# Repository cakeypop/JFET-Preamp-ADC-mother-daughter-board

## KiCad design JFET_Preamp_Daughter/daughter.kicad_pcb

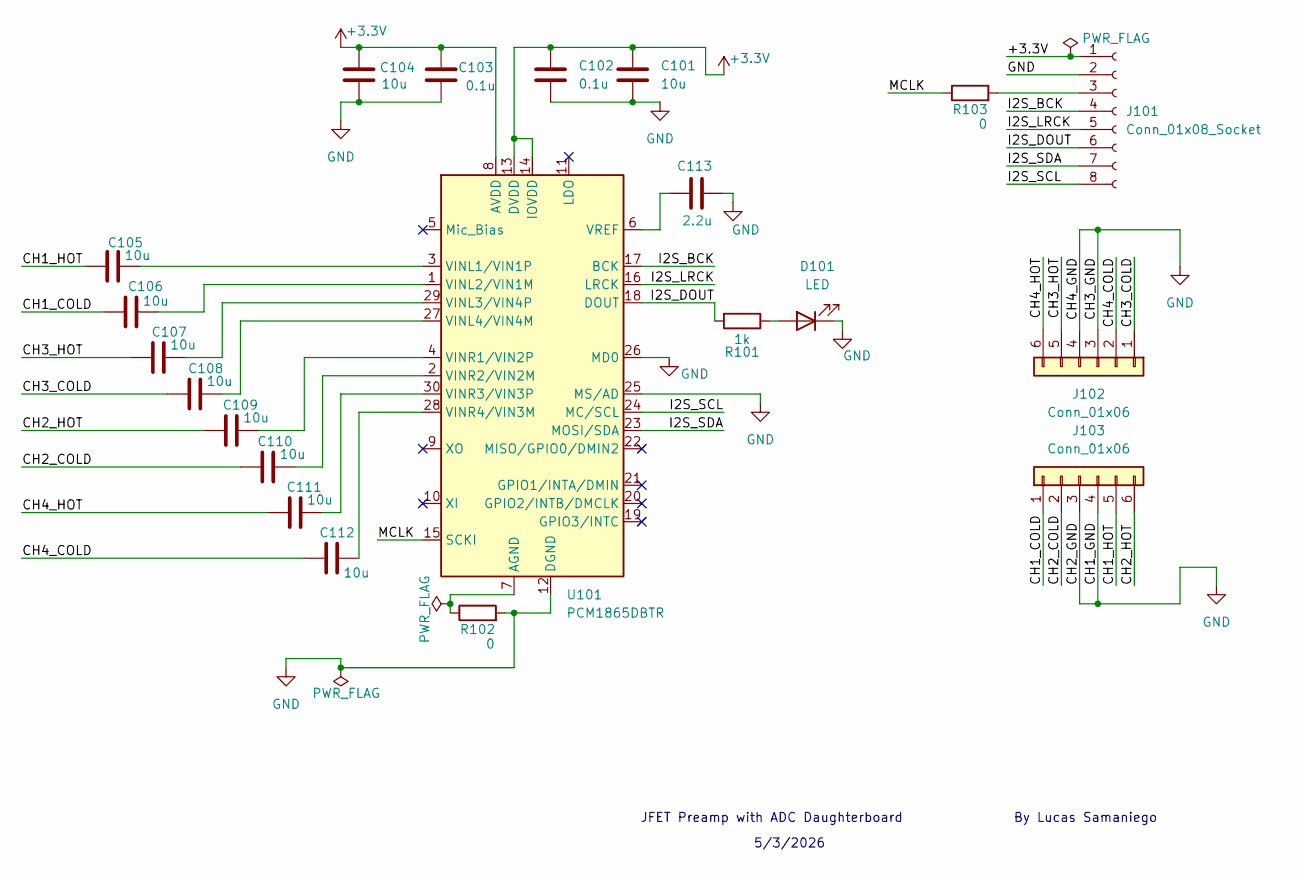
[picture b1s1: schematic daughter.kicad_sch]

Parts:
C101, C104, C105, C106, C107, C108, C109, C110, C111, C112: 10u; C_0402_1005Metric; LCSC Part # C15525
C102, C103: 0.1u; C_0402_1005Metric; LCSC Part # C1525
C113: 2.2u; C_0402_1005Metric; LCSC Part # C12530
D101: LED; LED_0603_1608Metric; LCSC Part # C2286
J101: Conn_01x08_Socket; JST_GH_BM08B-GHS-TBT_1x08-1MP_P1.25mm_Vertical
J102, J103: Conn_01x06; PinHeader_1x06_P2.54mm_Vertical
R101: 1k; R_0603_1608Metric; LCSC Part # C21190
R102, R103: 0; R_0603_1608Metric; LCSC Part # C21189
U101: PCM1865DBTR; TSSOP-30_4.4x7.8mm_P0.5mm; LCSC Part # C181312

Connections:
+3.3V: C101.1, C102.1, C103.1, C104.1, J101.1, U101.8 (AVDD), U101.13 (DVDD), U101.14 (IOVDD)
/CH1_COLD: C106.1, J103.1
/CH1_HOT: C105.1, J103.5
/CH2_COLD: C110.1, J103.2
/CH2_HOT: C109.1, J103.6
/CH3_COLD: C108.1, J102.1
/CH3_HOT: C107.1, J102.5
/CH4_COLD: C112.1, J102.2
/CH4_HOT: C111.1, J102.6
/I2S_BCK: J101.4, U101.17 (BCK)
/I2S_DOUT: J101.6, R101.2, U101.18 (DOUT)
/I2S_LRCK: J101.5, U101.16 (LRCK)
/I2S_SCL: J101.8, U101.24 (MC/SCL)
/I2S_SDA: J101.7, U101.23 (MOSI/SDA)
/MCLK: R103.1, U101.15 (SCKI)
GND: C101.2, C102.2, C103.2, C104.2, C113.2, D101.1 (K), J101.2, J102.3, J102.4, J103.3, J103.4, R102.2, U101.12 (DGND), U101.25 (MS/AD), U101.26 (MD0)
unnamed: D101.2 (A), R101.1
unnamed: J101.3, R103.2
unnamed: R102.1, U101.7 (AGND)
unnamed: C105.2, U101.3 (VINL1/VIN1P)
unnamed: C106.2, U101.1 (VINL2/VIN1M)
unnamed: C107.2, U101.29 (VINL3/VIN4P)
unnamed: C108.2, U101.27 (VINL4/VIN4M)
unnamed: C109.2, U101.4 (VINR1/VIN2P)
unnamed: C110.2, U101.2 (VINR2/VIN2M)
unnamed: C111.2, U101.30 (VINR3/VIN3P)
unnamed: C112.2, U101.28 (VINR4/VIN3M)
unnamed: C113.1, U101.6 (VREF)

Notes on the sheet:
JFET Preamp with ADC Daughterboard By Lucas Samaniego
5/3/2026

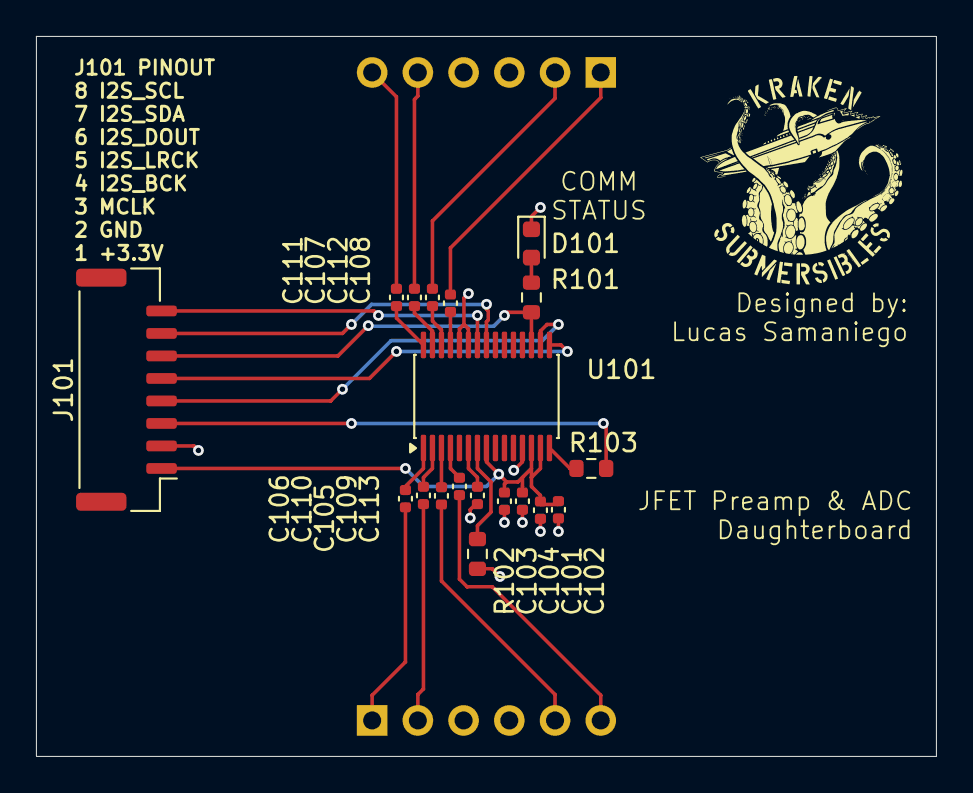
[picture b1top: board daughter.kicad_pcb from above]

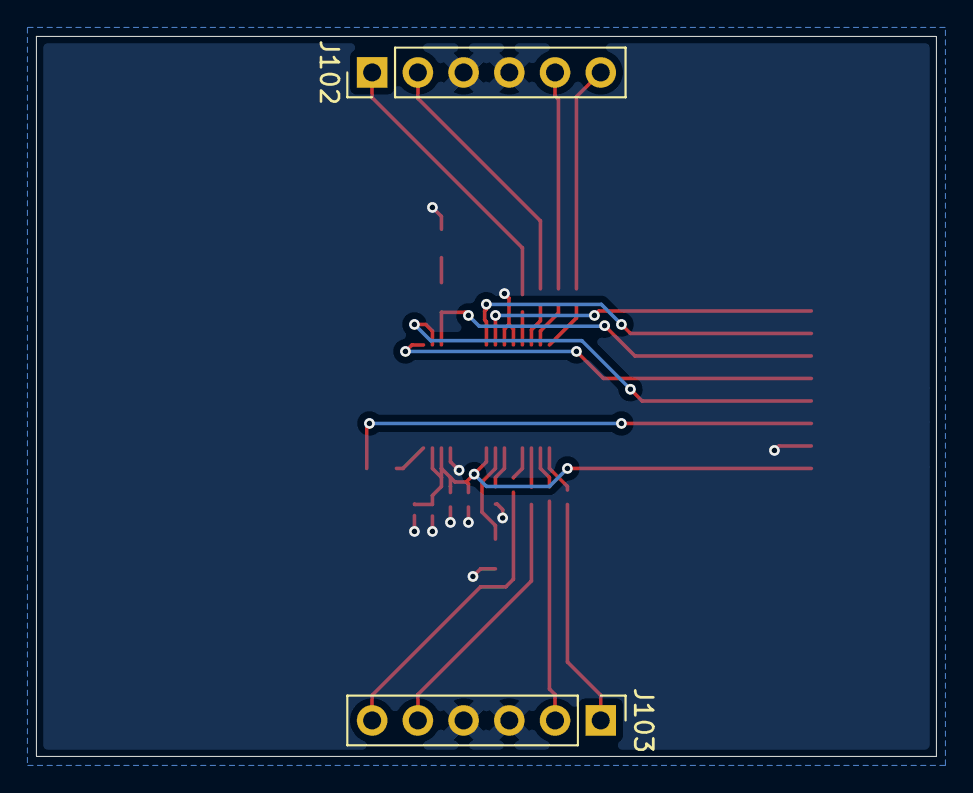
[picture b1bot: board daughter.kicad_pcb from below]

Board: 2 copper layers, 50.0 x 40.0 mm, 21 parts (2 on the bottom side), 28 nets.

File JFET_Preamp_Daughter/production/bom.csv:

Designator,Footprint,Quantity,Value,LCSC Part #
"C101, C104, C105, C106, C107, C108, C109, C110, C111, C112",0402,10,10u,C15525
"C102, C103",0402,2,0.1u,C1525 
C113,0402,1,2.2u,C12530
D101,0603,1,LED,C2286
R101,0603,1,1k,C21190
"R102, R103",0603,2,0,C21189
U101,TSSOP-30_4.4x7.8mm_P0.5mm,1,PCM1865DBTR,C181312

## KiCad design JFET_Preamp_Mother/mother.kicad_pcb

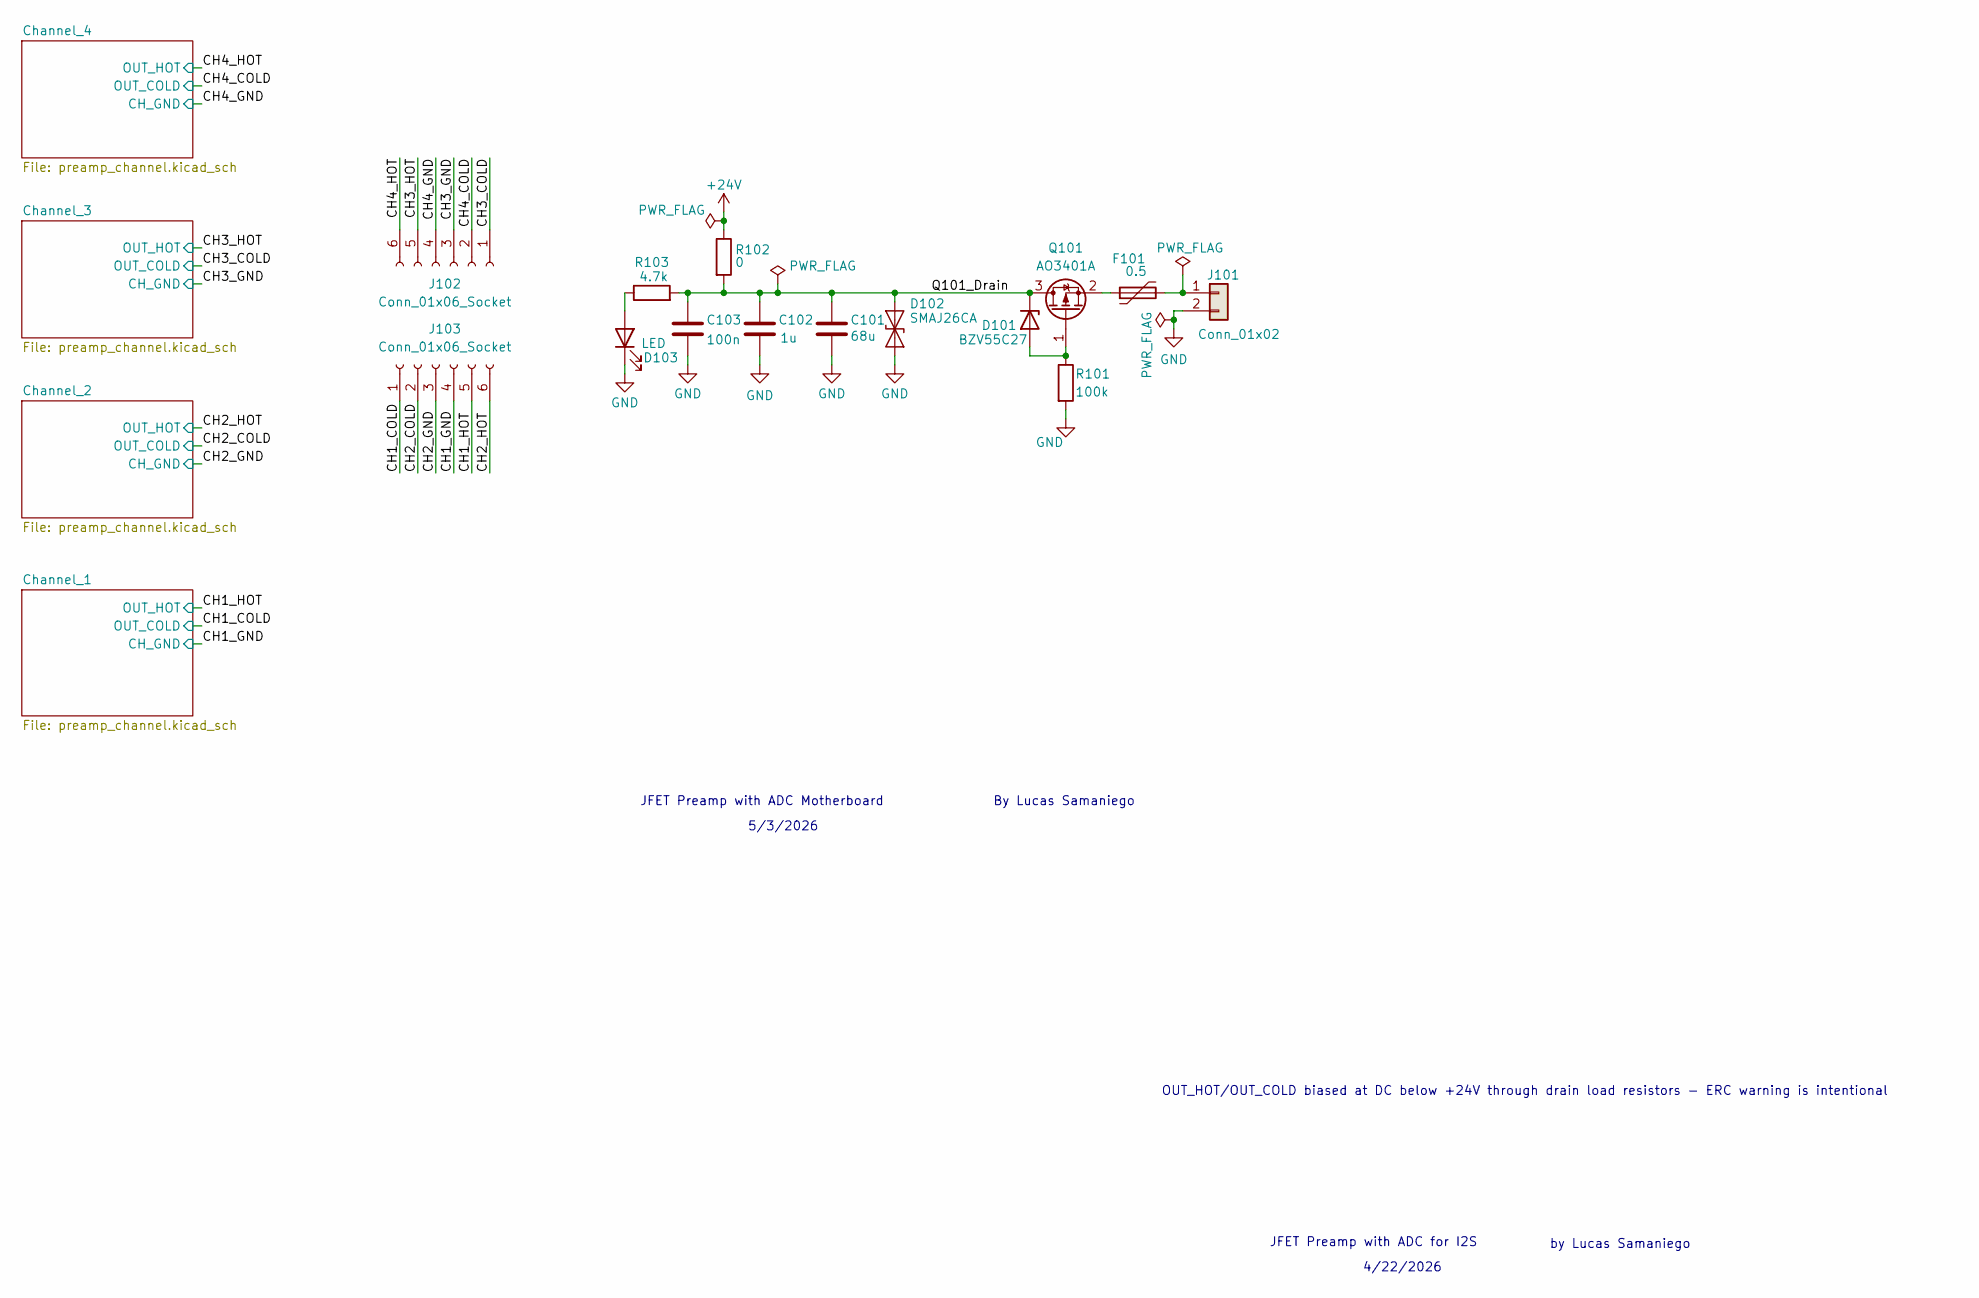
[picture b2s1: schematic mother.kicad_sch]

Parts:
C101: 68u; CP_Elec_6.3x5.4
C102: 1u; C_0603_1608Metric; LCSC Part # C15849
C103: 100n; C_0603_1608Metric; LCSC Part # C14663
D101: BZV55C27; D_MiniMELF; LCSC Part # C545374
D102: SMAJ26CA; D_SMA; LCSC Part # C148226
D103: LED; LED_0603_1608Metric; LCSC Part # C2286
F101: 0.5; FUSRB510W51L790T310H1370
J101: Conn_01x02; PinHeader_1x02_P2.54mm_Vertical
J102, J103: Conn_01x06_Socket; PinSocket_1x06_P2.54mm_Vertical
Q101: AO3401A; SOT-23; LCSC Part # C15127
R101: 100k; R_0603_1608Metric; LCSC Part # C25803
R102: 0; R_0603_1608Metric; LCSC Part # C21189
R103: 4.7k; R_0603_1608Metric; LCSC Part # C25999

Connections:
+24V: R102.1; also elsewhere on the board
/CH1_COLD: J103.1; also elsewhere on the board
/CH1_GND: J103.4; also elsewhere on the board
/CH1_HOT: J103.5; also elsewhere on the board
/CH2_COLD: J103.2; also elsewhere on the board
/CH2_GND: J103.3; also elsewhere on the board
/CH2_HOT: J103.6; also elsewhere on the board
/CH3_COLD: J102.1; also elsewhere on the board
/CH3_GND: J102.3; also elsewhere on the board
/CH3_HOT: J102.5; also elsewhere on the board
/CH4_COLD: J102.2; also elsewhere on the board
/CH4_GND: J102.4; also elsewhere on the board
/CH4_HOT: J102.6; also elsewhere on the board
/Q101_Drain: C101.1, C102.1, C103.1, D101.1 (K), D102.2 (A2), Q101.3 (D), R102.2, R103.2
GND: C101.2, C102.2, C103.2, D102.1 (A1), D103.1 (K), J101.2, R101.2
unnamed: D101.2 (A), Q101.1 (G), R101.1
unnamed: D103.2 (A), R103.1
unnamed: F101.2, J101.1
unnamed: F101.1, Q101.2 (S)

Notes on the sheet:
OUT_HOT/OUT_COLD biased at DC below +24V through drain load resistors - ERC warning is intentional
JFET Preamp with ADC for I2S
5/3/2026
by Lucas Samaniego
JFET Preamp with ADC Motherboard By Lucas Samaniego
4/22/2026

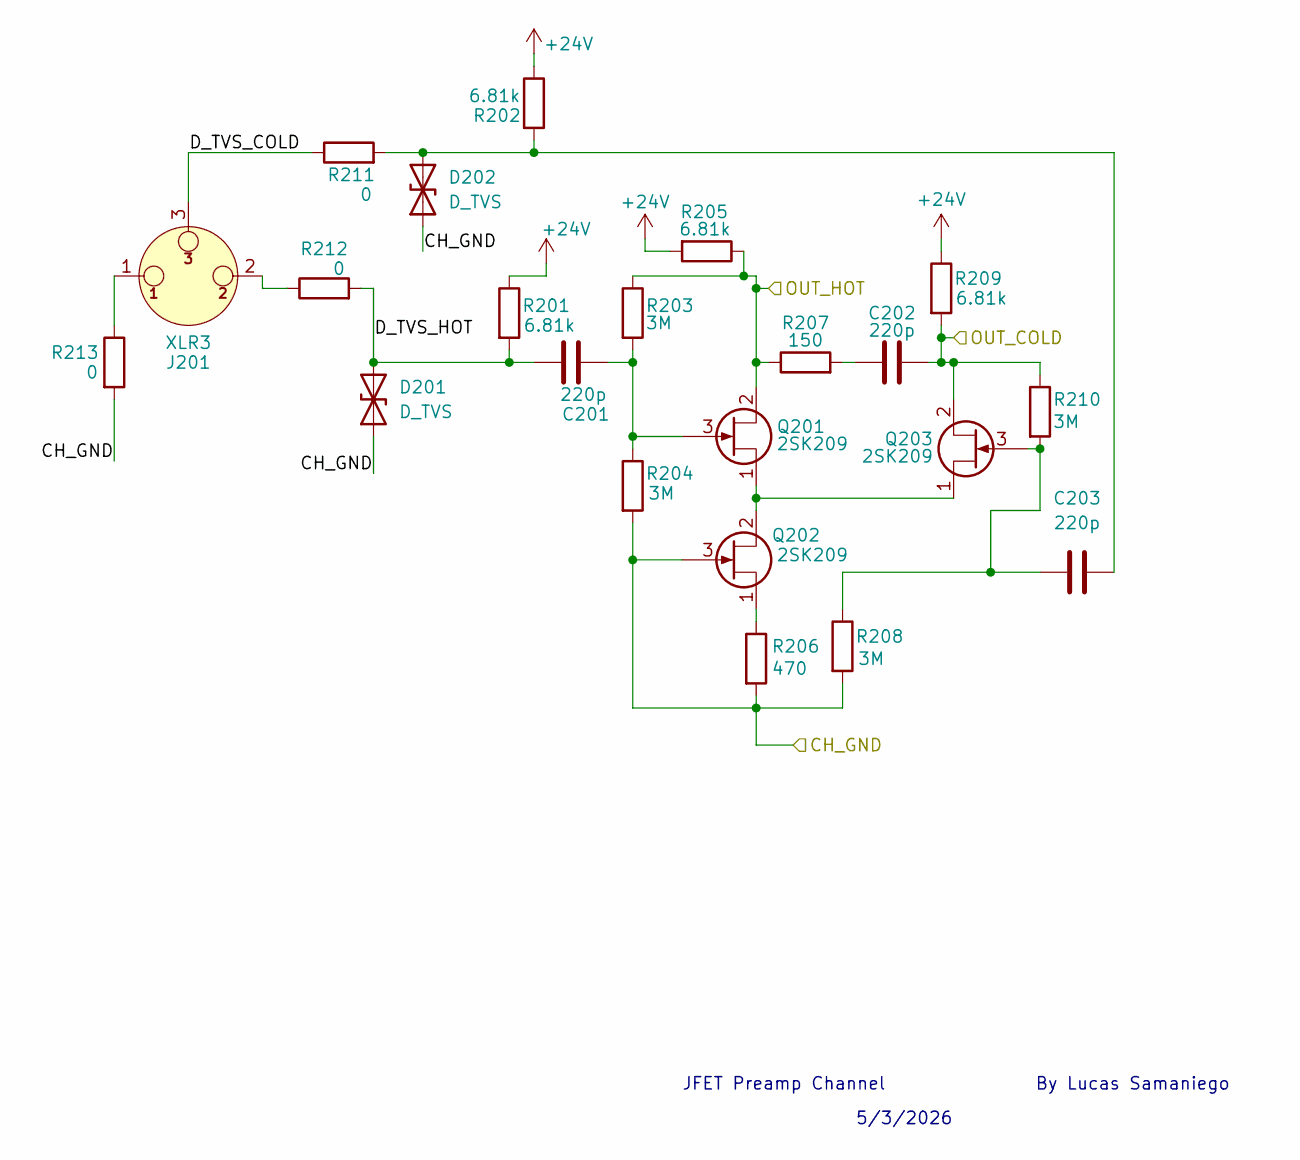
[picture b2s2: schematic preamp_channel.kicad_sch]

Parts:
C201, C202, C203: 220p; C_0603_1608Metric; LCSC Part # C1603
D201, D202: D_TVS; D_SMA; LCSC Part # C148226
J201: XLR3; Jack_XLR_Neutrik_NC3FAH1_Horizontal
Q201, Q202, Q203: 2SK209; SOT-23; LCSC Part # C2880444
R201, R202, R205, R209: 6.81k; R_0603_1608Metric; LCSC Part # C137687
R203, R204, R208, R210: 3M; R_0603_1608Metric; LCSC Part # C23156
R206: 470; R_0603_1608Metric; LCSC Part # C25117
R207: 150; R_0603_1608Metric; LCSC Part # C22808
R211, R212, R213: 0; R_0603_1608Metric; LCSC Part # C21189

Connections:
+24V: R201.1, R202.1, R205.2, R209.1; also elsewhere on the board
/CH1_COLD: C202.2, Q203.2 (D), R209.2, R210.1; also elsewhere on the board
/CH1_GND: D201.1 (A1), D202.1 (A1), Q202.3 (G), R204.2, R206.2, R208.2, R213.2; also elsewhere on the board
/CH1_HOT: Q201.2 (D), R203.1, R205.1, R207.1; also elsewhere on the board
/Channel_1/D_TVS_COLD: J201.3, R211.1
/Channel_1/D_TVS_HOT: C201.1, D201.2 (A2), R201.2, R212.2
unnamed: C202.1, R207.2
unnamed: C203.2, D202.2 (A2), R202.2, R211.2
unnamed: J201.1, R213.1
unnamed: J201.2, R212.1
unnamed: C201.2, Q201.3 (G), R203.2, R204.1
unnamed: Q201.1 (S), Q202.2 (D), Q203.1 (S)
unnamed: Q202.1 (S), R206.1
unnamed: C203.1, Q203.3 (G), R208.1, R210.2

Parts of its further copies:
C301, C302, C303, C401, C402, C403, C501, C502, C503: 220p; C_0603_1608Metric; LCSC Part # C1603
D301, D302, D401, D402, D501, D502: D_TVS; D_SMA; LCSC Part # C148226
J301, J401, J501: XLR3; Jack_XLR_Neutrik_NC3FAH1_Horizontal
Q301, Q302, Q303, Q401, Q402, Q403, Q501, Q502, Q503: 2SK209; SOT-23; LCSC Part # C2880444
R301, R302, R305, R309, R401, R402, R405, R409, R501, R502, R505, R509: 6.81k; R_0603_1608Metric; LCSC Part # C137687
R303, R304, R308, R310, R403, R404, R408, R410, R503, R504, R508, R510: 3M; R_0603_1608Metric; LCSC Part # C23156
R306, R406, R506: 470; R_0603_1608Metric; LCSC Part # C25117
R307, R407, R507: 150; R_0603_1608Metric; LCSC Part # C22808
R311, R312, R313, R411, R412, R413, R511, R512, R513: 0; R_0603_1608Metric; LCSC Part # C21189

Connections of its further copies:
+24V: R301.1, R302.1, R305.2, R309.1, R401.1, R402.1, R405.2, R409.1, R501.1, R502.1, R505.2, R509.1; also elsewhere on the board
/CH2_COLD: C302.2, Q303.2 (D), R309.2, R310.1; also elsewhere on the board
/CH2_GND: D301.1 (A1), D302.1 (A1), Q302.3 (G), R304.2, R306.2, R308.2, R313.2; also elsewhere on the board
/CH2_HOT: Q301.2 (D), R303.1, R305.1, R307.1; also elsewhere on the board
/CH3_COLD: C402.2, Q403.2 (D), R409.2, R410.1; also elsewhere on the board
/CH3_GND: D401.1 (A1), D402.1 (A1), Q402.3 (G), R404.2, R406.2, R408.2, R413.2; also elsewhere on the board
/CH3_HOT: Q401.2 (D), R403.1, R405.1, R407.1; also elsewhere on the board
/CH4_COLD: C502.2, Q503.2 (D), R509.2, R510.1; also elsewhere on the board
/CH4_GND: D501.1 (A1), D502.1 (A1), Q502.3 (G), R504.2, R506.2, R508.2, R513.2; also elsewhere on the board
/CH4_HOT: Q501.2 (D), R503.1, R505.1, R507.1; also elsewhere on the board
/Channel_2/D_TVS_COLD: J301.3, R311.1
/Channel_2/D_TVS_HOT: C301.1, D301.2 (A2), R301.2, R312.2
/Channel_3/D_TVS_COLD: J401.3, R411.1
/Channel_3/D_TVS_HOT: C401.1, D401.2 (A2), R401.2, R412.2
/Channel_4/D_TVS_COLD: J501.3, R511.1
/Channel_4/D_TVS_HOT: C501.1, D501.2 (A2), R501.2, R512.2
unnamed: C302.1, R307.2
unnamed: C402.1, R407.2
unnamed: C502.1, R507.2
unnamed: C303.2, D302.2 (A2), R302.2, R311.2
unnamed: C403.2, D402.2 (A2), R402.2, R411.2
unnamed: C503.2, D502.2 (A2), R502.2, R511.2
unnamed: J301.1, R313.1
unnamed: J301.2, R312.1
unnamed: J401.1, R413.1
unnamed: J401.2, R412.1
unnamed: J501.1, R513.1
unnamed: J501.2, R512.1
unnamed: C301.2, Q301.3 (G), R303.2, R304.1
unnamed: Q301.1 (S), Q302.2 (D), Q303.1 (S)
unnamed: Q302.1 (S), R306.1
unnamed: C303.1, Q303.3 (G), R308.1, R310.2
unnamed: C401.2, Q401.3 (G), R403.2, R404.1
unnamed: Q401.1 (S), Q402.2 (D), Q403.1 (S)
unnamed: Q402.1 (S), R406.1
unnamed: C403.1, Q403.3 (G), R408.1, R410.2
unnamed: C501.2, Q501.3 (G), R503.2, R504.1
unnamed: Q501.1 (S), Q502.2 (D), Q503.1 (S)
unnamed: Q502.1 (S), R506.1
unnamed: C503.1, Q503.3 (G), R508.1, R510.2

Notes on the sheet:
5/3/2026
JFET Preamp Channel By Lucas Samaniego

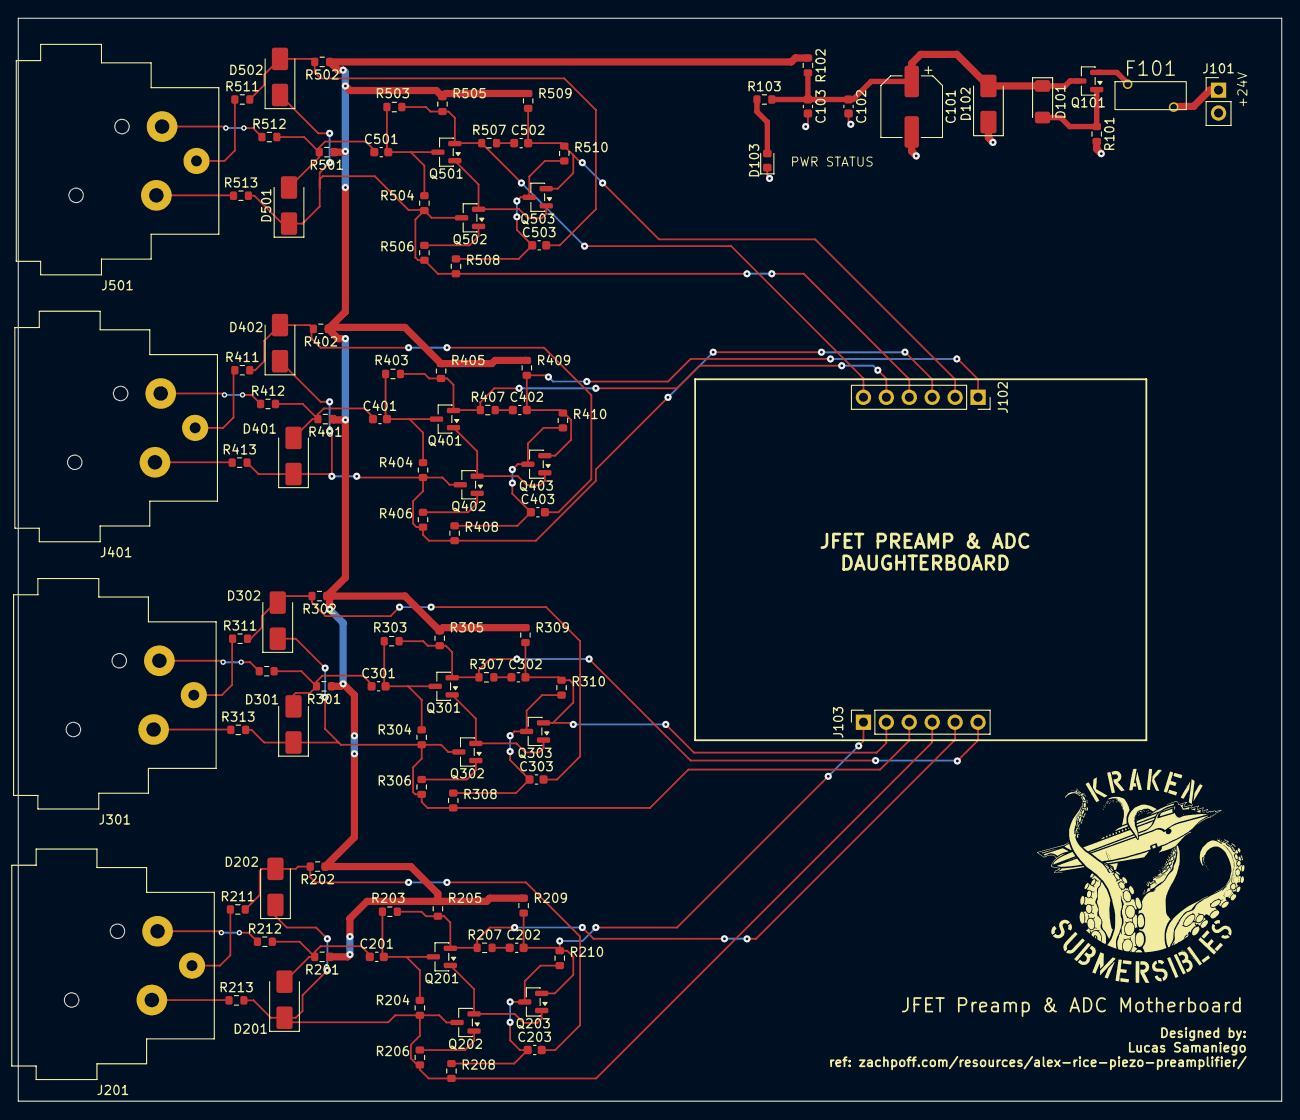
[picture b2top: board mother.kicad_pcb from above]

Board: 2 copper layers, 140.0 x 120.0 mm, 102 parts (0 on the bottom side), 59 nets.

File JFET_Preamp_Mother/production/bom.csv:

Designator,Footprint,Quantity,Value,LCSC Part #
C102,0603,1,1u,C15849
C103,0603,1,100n,C14663
"C201, C202, C203, C301, C302, C303, C401, C402, C403, C501, C502, C503",0603,12,220p,C1603
D101,D_MiniMELF,1,BZV55C27,C545374
D102,D_SMA,1,SMAJ26CA,C148226
D103,0603,1,LED,C2286
"D201, D202, D301, D302, D401, D402, D501, D502",D_SMA,8,D_TVS,C148226 
Q101,SOT-23,1,AO3401A,C15127
"Q201, Q202, Q203, Q301, Q302, Q303, Q401, Q402, Q403, Q501, Q502, Q503",SOT-23,12,2SK209,C2880444
R101,0603,1,100k,C25803
"R102, R211, R212, R213, R311, R312, R313, R411, R412, R413, R511, R512, R513",0603,13,0,C21189
R103,0603,1,4.7k,C25999
"R201, R202, R205, R209, R301, R302, R305, R309, R401, R402, R405, R409, R501, R502, R505, R509",0603,16,6.81k,C137687
"R203, R204, R208, R210, R303, R304, R308, R310, R403, R404, R408, R410, R503, R504, R508, R510",0603,16,3M,C23156
"R206, R306, R406, R506",0603,4,470,C25117
"R207, R307, R407, R507",0603,4,150,C22808

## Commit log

2026-06-17 Re-Initial commit after errors - mobo/daughter projects
2026-06-17 motherboard .sch erc clean
2026-06-17 Remove KiCad lock files from tracking, update gitignore
2026-06-17 Remove VS Code history folders and stray file from tracking
2026-06-17 Remove mother .history folder from tracking
2026-06-17 move MF-R050 footprint library into repo to use relative path
2026-06-17 daugter removed unused copy of preamp_channel.sch not used in daughterboard
2026-06-18 slight details update to daughter
2026-06-18 finish draft of mother/daughter sch and start routing, reconcile libraries and missing footprints
2026-06-18 adding a few minor edits
2026-06-19 finish routing daughterboard and fix 0 ohm resistor on AGND/DGND for schematic
2026-06-19 add silkscreen to pcb daughterboard, possibly final pending review
2026-06-19 fix ERC on schematic, then proceed to begin routing on pcb
2026-06-19 forgot to save ERC change adding pwr flag to mother sch
2026-06-24 push just to make sure everything is up to date
2026-06-30 WIP motherboard pcb save point, layout and partial routing complete
2026-06-30 fix backwards J102 on daughterboard to match schematic and mother/daughter pairing
2026-06-30 finished pcb, updated schematic formatting, ready for fab
2026-06-30 small updates to schematic before adjusting/printing pdf
2026-06-30 further adjustments to sch/pcb
2026-06-30 fixed wrong-facing 6pin connector and redo GND pour
2026-06-30 generate gerber and drill files
2026-06-30 fix error in gerber, extra layers
2026-06-30 regenerate mother gerber and drill
2026-06-30 fixed TVS Diodes across 4 channels and redo placement and traces
2026-06-30 finished for first fab Mother order, pending daughter
2026-06-30 update Capacitors to better suit and rebuild, prep for fab, final for 1st fab
2026-06-30 small changes to pcb
